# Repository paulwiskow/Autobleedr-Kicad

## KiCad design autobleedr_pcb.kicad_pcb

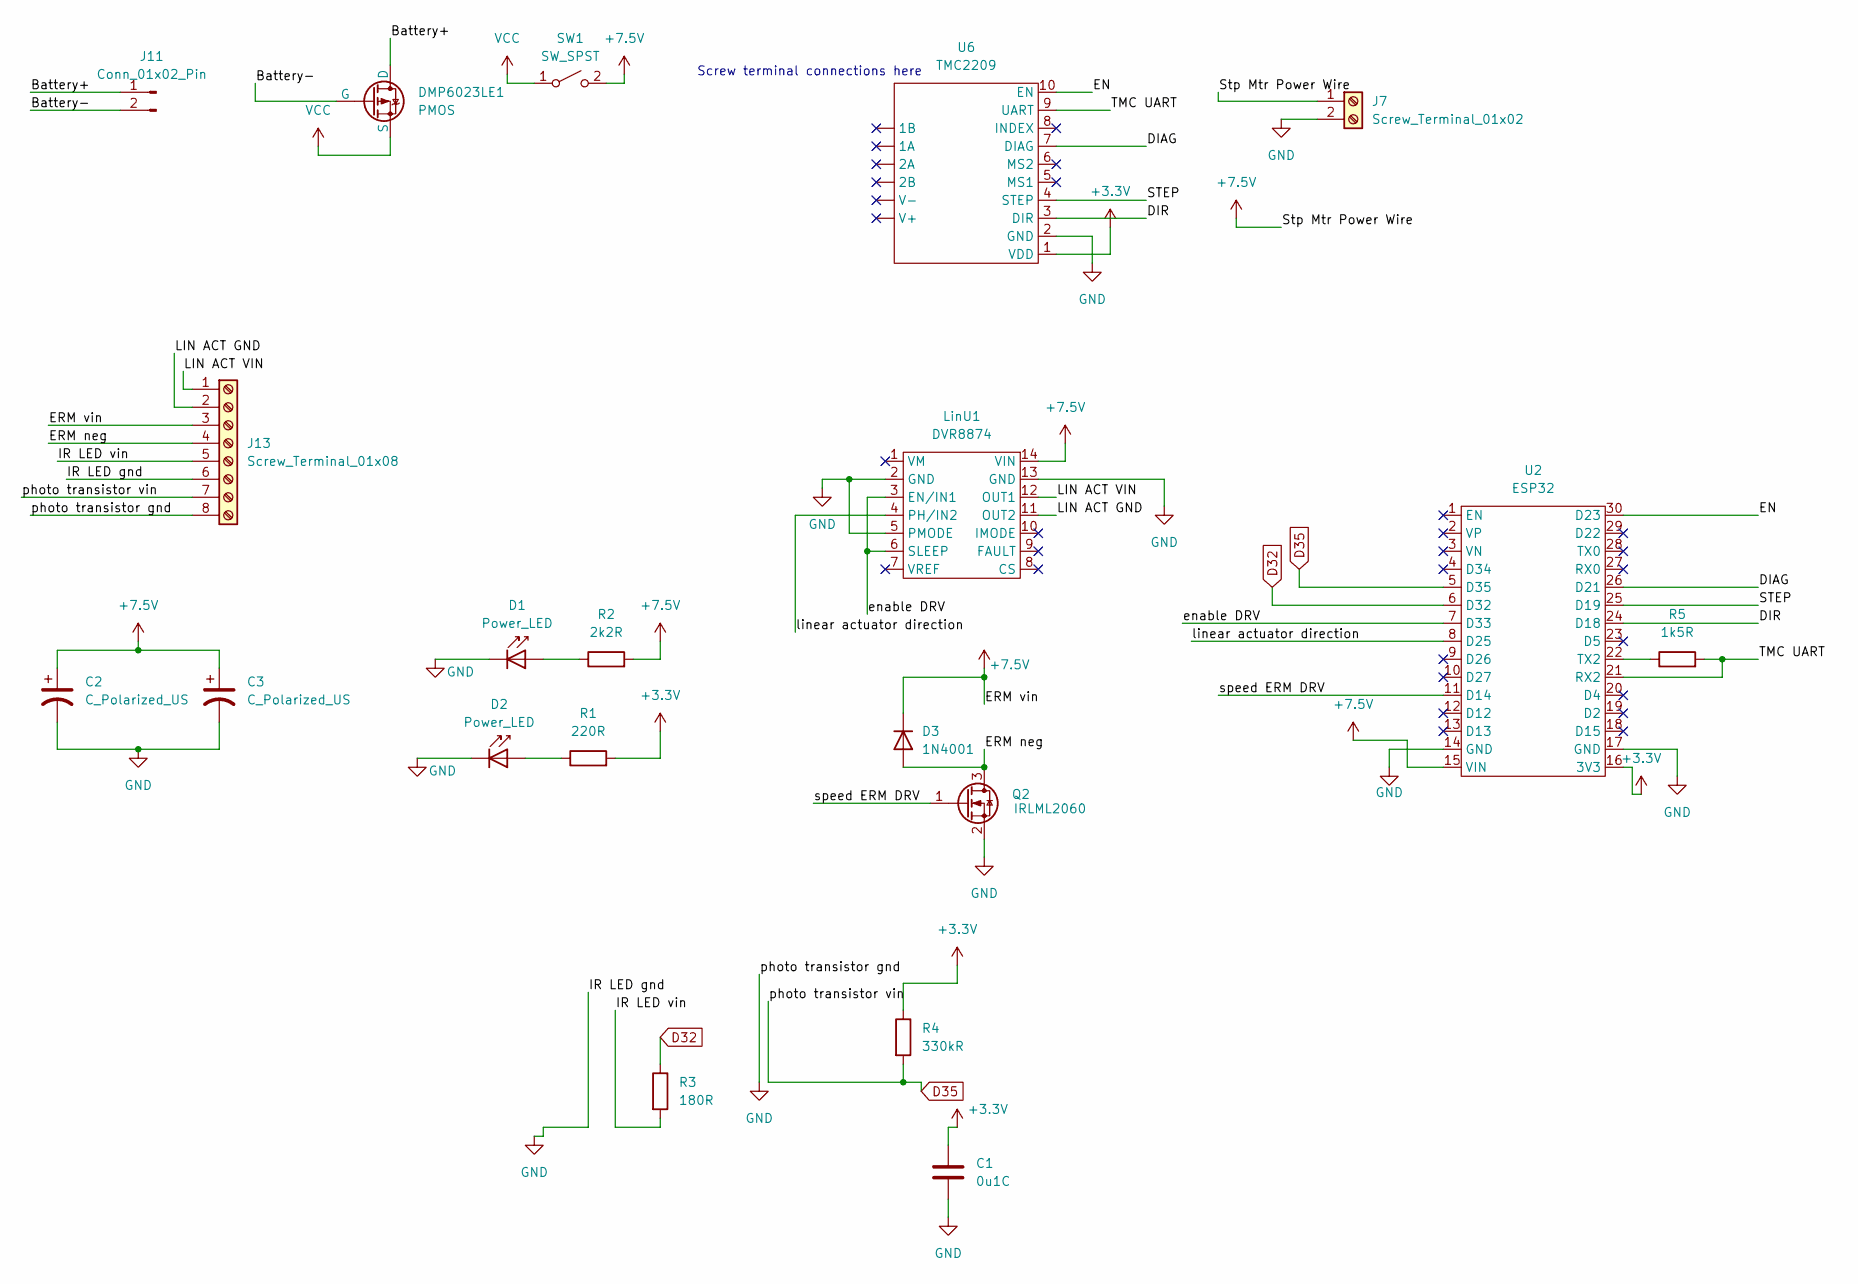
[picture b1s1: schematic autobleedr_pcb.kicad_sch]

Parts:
C1: 0u1C; C_Axial_L5.1mm_D3.1mm_P7.50mm_Horizontal
C2, C3: C_Polarized_US; CP_Radial_D8.0mm_P5.00mm
D1, D2: Power_LED; LED_D5.0mm_IRGrey
D3: 1N4001; D_DO-41_SOD81_P10.16mm_Horizontal
DMP6023LE1: PMOS; DMP6023LE
J7: Screw_Terminal_01x02; TerminalBlock_MaiXu_MX126-5.0-02P_1x02_P5.00mm
J11: Conn_01x02_Pin; PinHeader_1x02_P2.54mm_Vertical
J13: Screw_Terminal_01x08; Screw_Terminal_1x8
LinU1: DVR8874
Q2: IRLML2060; SOT-23
R1: 220R; R_Axial_DIN0207_L6.3mm_D2.5mm_P7.62mm_Horizontal
R2: 2k2R; R_Axial_DIN0207_L6.3mm_D2.5mm_P7.62mm_Horizontal
R3: 180R; R_Axial_DIN0207_L6.3mm_D2.5mm_P7.62mm_Horizontal
R4: 330kR; R_Axial_DIN0207_L6.3mm_D2.5mm_P7.62mm_Horizontal
R5: 1k5R; R_Axial_DIN0207_L6.3mm_D2.5mm_P7.62mm_Horizontal
SW1: SW_SPST; R1966ABLKBLKGR
U2: ESP32
U6: TMC2209

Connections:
+3.3V: C1.1, R1.2, R4.1, U2.16 (3V3), U6.1 (VDD)
+7.5V: C2.1, C3.1, D3.1 (K), J7.1, J13.3, LinU1.14 (VIN), R2.2, SW1.2 (B), U2.15 (VIN)
/Battery+: DMP6023LE1.4 (D), J11.1
/Battery-: DMP6023LE1.1 (G), J11.2
/DIAG: U2.26 (D21), U6.7 (DIAG)
/DIR: U2.24 (D18), U6.3 (DIR)
/EN: U2.30 (D23), U6.10 (EN)
/ERM neg: D3.2 (A), J13.4, Q2.3 (D)
/IR LED vin: J13.5, R3.2
/LIN ACT GND: J13.2, LinU1.11 (OUT2)
/LIN ACT VIN: J13.1, LinU1.12 (OUT1)
/STEP: U2.25 (D19), U6.4 (STEP)
/TMC UART: R5.2, U2.21 (RX2), U6.9 (UART)
/enable DRV: LinU1.3 (EN/IN1), LinU1.6 (SLEEP), U2.7 (D33)
/linear actuator direction: LinU1.4 (PH/IN2), U2.8 (D25)
/speed ERM DRV: Q2.1 (G), U2.11 (D14)
D32: R3.1, U2.6 (D32)
D35: J13.7, R4.2, U2.5 (D35)
GND: C1.2, C2.2, C3.2, D1.1 (K), D2.1 (K), J7.2, J13.6, J13.8, LinU1.2 (GND), LinU1.5 (PMODE), LinU1.13 (GND), Q2.2 (S), U2.14 (GND), U2.17 (GND), U6.2 (GND)
unnamed: D1.2 (A), R2.1
unnamed: D2.2 (A), R1.1
unnamed: R5.1, U2.22 (TX2)
VCC: DMP6023LE1.3 (S), SW1.1 (A)

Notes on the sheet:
Screw terminal connections here

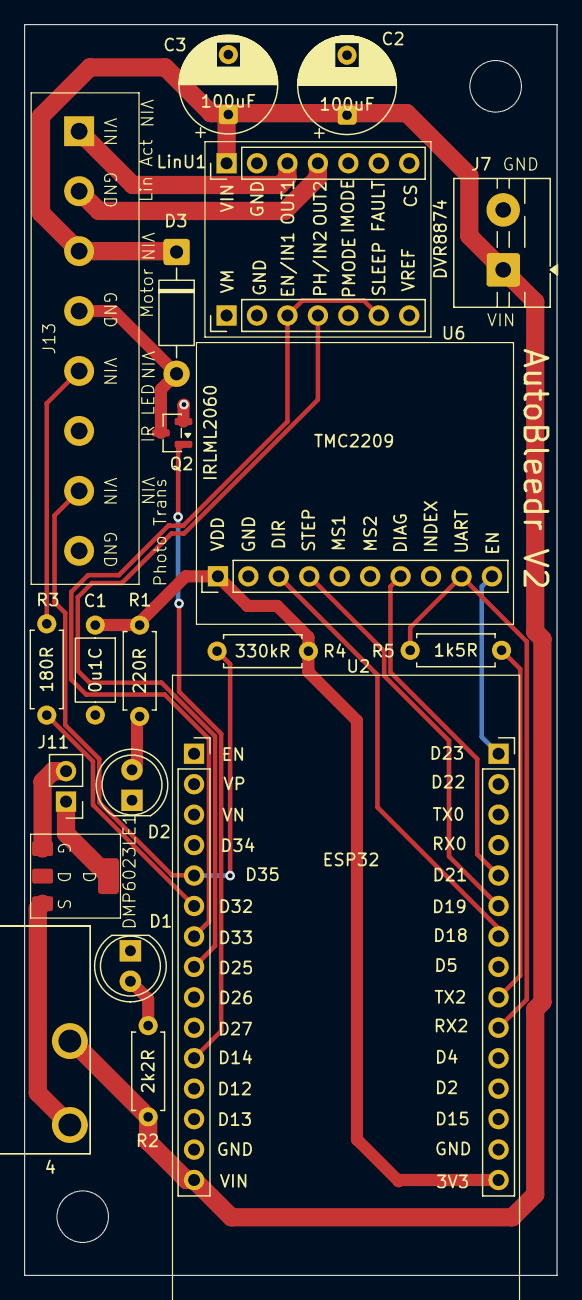
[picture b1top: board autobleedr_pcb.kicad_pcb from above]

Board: 4 copper layers, 44.4 x 104.3 mm, 22 parts (0 on the bottom side), 23 nets.

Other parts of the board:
2, 4: MountingHole_4.3mm_M4_ISO7380_Pad

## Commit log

2025-10-05 Added all project files
2025-10-05 added header pins
2025-10-05 finished initial PCB
2025-10-11 resubmit update 1
2025-10-13 Updated buck converter footprint, added stitching vias, test points, traces
2025-10-14 save merge
2025-10-15 finished labels, screw holes, and trace widths
2025-10-21 updated pcb with DRV and working on compressing PCB itself:
2025-10-21 compressed PCB more
2025-10-22 updated schematic
2025-10-24 Added ERM PCB schematic
2025-10-24 Cleaned up wires
2025-10-24 Redid symbols and footprints properly
2025-10-25 added Select Battery aka On Off Switch and power indicator LED with current limiting resistor
2025-10-25 updated PCB
2025-10-25 added most traces
2025-10-29 Rerouted board and changed some gpio pins, added 3.3 led
2025-10-29 Made some slight adjustments in morning meetingg
2025-10-30 added label for switch
2025-10-30 Added bulk capacitors
2025-10-31 finishing touches
2025-10-31 Made some changes for Barnes
2025-11-18 updated v2
2025-11-20 Initial plan
2025-11-21 Added uart connection
2025-11-21 updated board with new battery and v2 traces
2025-11-21 Added UART Resistor and the modified ERM driver.
2025-11-22 updated pcb traces with binh nmos design
2025-11-22 Added another rendition to the pcb layout
2025-11-22 Redid pcb
2025-11-23 Added EN pin and c1
2025-11-25 Update bubble circuit
2025-11-26 updated with Bens recommendations
2025-11-26 Added some silkscreen changes
2025-11-27 Reset origin
2025-12-07 added to silkscreen
